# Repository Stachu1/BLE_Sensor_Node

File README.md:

# BLE Sensor Node

**BEng in Electronics Engineering thesis project, focused on low-power design and RF performance.**

A compact, coin-cell-powered Bluetooth Low Energy sensor node that measures temperature and humidity and broadcasts
the data as [BTHome](https://bthome.io/) advertisements, without needing a persistent connection.

*Rev A: `BSN-N54-A` (left), `BSN-C23-A` (middle) and the back of `BSN-C23-A` with the coin-cell holder.*

## Goal

Keep the average current low enough for multi-year operation on a single CR2032 cell, in a compact size. Main areas
of work: low-power firmware and advertising strategy, antenna/RF performance (chip vs. trace antenna), and power
budgeting around the coin cell's current limits.

## Highlights

- **Two MCUs designed, built and measured side by side** on rev A: Nordic nRF54L05 (`BSN-N54`) and TI CC2340R5
  (`BSN-C23`), with the same sensors, antenna and board outline. The CC2340R5 was chosen for rev B, mainly on sleep
  current and with RF performance as a second factor ([`MCU_DECISION.md`](hardware/MCU_DECISION.md)).
- **0.37 µA sleep floor** on BSN-C23-A, below the CC2340R5's own datasheet typical. Every event (advert, sensor
  reading, cold boot) was measured as a charge, which gives a current model for any setting: about 3.3 µA at a
  5 s advertising interval, or roughly 7 years on a 225 mAh CR2032 before derating
  ([power measurements](hardware/C23/testing/rev_A/Power/POWER_MEASUREMENTS.md)).
- **Rev A chip antenna matched on the VNA**, step by step from the unmatched antenna, with the board lifted off the
  bench (the wooden table under it had detuned the antenna) ([antenna matching](hardware/C23/testing/rev_A/RF/ANTENNA_MATCHING.md)).
- **Conducted harmonics measured on a spectrum analyser** against the FCC restricted-band limit. With no filter on
  either board, both fail on H3, the C23 by 0.6 dB and the N54 by 17 dB. With the simple pi network from TI's
  reference design the C23 passes with 9.5 dB margin. The N54's PA network, adapted from Nordic's reference design
  with 0402 parts, cost about 10 dB of output power, so it was bypassed for the measurements
  ([C23](hardware/C23/testing/rev_A/RF/RF_CARRIER.md), [N54](hardware/N54/testing/RF/RF_CARRIER.md)).
- **Rev B trace antenna designed in openEMS on the real board.** A scripted pipeline exports the KiCad board
  (all four copper layers, vias, stack-up, the CR2032) to the FDTD solver on a compute server. The chosen
  inverted-F antenna simulates at −14.9 dB S11 or better across the BLE band with two matching parts, and 85 to 89 %
  total efficiency. Simulated only, the rev B boards have not been measured yet
  ([antenna write-up](hardware/C23/testing/RF/antenna_C23-B/README.md), [simulation pipeline](hardware/C23/testing/RF/sim/README.md)).
- **Firmware for both MCUs** written to the same structure (bring-up self-test, BLE sensor, CW RF test, one power
  state per build) so the two can be measured the same way.

## Design

| `BSN-C23-B` (TI CC2340R5) | `BSN-N54-A` (Nordic nRF54L05) |
|---|---|
|  |  |
| [Schematic](hardware/C23/schematic.pdf) · [PCB](hardware/C23/PCB.pdf) · [README](hardware/C23/README.md) | [Schematic](hardware/N54/schematic.pdf) · [PCB](hardware/N54/PCB.pdf) · [README](hardware/N54/README.md) |

4-layer, 34 × 34 mm board with an HDC2010 temperature/humidity sensor, the CR2032 holder on the back and test
points for SWD, UART, I2C and the sensor interrupt.

- **Rev A (both variants):** 15.5 mm corner radii (close to round), chip antenna with a pi matching network, an
  optional U.FL connector for conducted RF tests and an SHTC3 footprint as an alternative sensor.
- **Rev B (C23 only):** 10 mm corner radii, an inverted-F antenna printed on the top layer, an MM8130 switch
  connector for VNA measurements of the antenna match, a Tag-Connect footprint for SWD, UART TX and a BOOT pin for
  the ROM bootloader, and a 0 Ω link in the supply for the ammeter. The pi network is unchanged from rev A.

## Status

Rev A of both variants was compared (thesis test T0). **Rev B uses the TI CC2340R5 (`BSN-C23-B`)** with a PCB trace
antenna, and the N54 variant stops at rev A. Rev B was ordered on 2026-11-04 (tag `hw/BSN-C23-B`). A rev C will
only be made if the rev B tests show it is needed and there is time.

The main reason is the sleep current, which sets the average current at a 5 s or slower advertising interval. RF
was also taken into account. The C23 already passes the harmonics limit with the simple pi network from TI's
reference design, so rev B starts from an RF chain that works. The N54 would need a new harmonic filter and another
RF iteration.

| | `BSN-C23-A` | `BSN-N54-A` |
|---|---|---|
| Sleep floor | 0.366 µA | 4.20 µA (System OFF 2.05 µA, both about 1.4 µA above the datasheet, cause not found) |
| Charge per advert, 0 dBm | 12.6 µC | 7.6 µC |
| Charge per sensor reading, timer / DRDY wake | 9.56 / 3.72 µC | 2.01 / 1.78 µC |
| Conducted power at the 0 dBm setting | −2.1 dBm | 0.0 dBm (PA network bypassed) |
| Harmonics with no filter, 0 dBm (conducted, FCC restricted-band limit −41.2 dBm) | H3 −40.6 dBm, fails by 0.6 dB | H3 −24.3 dBm, fails by 17 dB |
| Harmonic filter | Pi network from TI's reference design. Passes at +8 dBm (2440 and 2480 MHz) with 9.5 dB margin (H5) | PA network adapted from Nordic's reference design with 0402 parts. Lost 10–11 dB of output power and was bypassed. No working filter on this layout |
| Notes | [`hardware/C23/testing`](hardware/C23/testing) | [`hardware/N54/testing`](hardware/N54/testing) |

Rev A boards:

| Board | MCU | Status |
|---|---|---|
| `BSN-N54-A` | nRF54L05 | Ordered and assembled (2 boards). Board #1 advertising BTHome. Board #2 (U.FL): HFXO trimmed to 11.75 pF, PA network bypassed (the rev A layout of it loses 10 dB), 0.0 dBm at the 0 dBm setting. Floor 4.20 µA, 7.6 µC per advert |
| `BSN-C23-A` | CC2340R5 | Ordered and assembled. Board #1 flashed and advertising BTHome, antenna matched with the board lifted off the bench (L2 4.3 nH, L3 2.1 pF). Floor 0.366 µA, 12.6 µC per advert, about 20 µC per payload reload in the TI stack. CW boards with and without the PA pi network |

Open questions:

- The N54 floor sits about 1.4 µA above the datasheet on both boards. Not needed for the MCU choice, but still being
  looked into for the thesis.

### Next

- **Rev B bring-up** (`BSN-C23-B`): VNA match of the trace antenna against the simulation, the full-firmware check
  at a 5 s interval, the CR2032 VDD dip during TX and the H5 margin with the trace antenna.
- **Rev C** (optional): only if rev B needs fixes and time allows.
- Battery tests on fresh boards with a real CR2032, line-of-sight range tests and radiated measurements.

## Repository Structure

```
hardware/
  MCU_DECISION.md   Why rev B uses the CC2340R5
  C23/              BSN-C23 - TI CC2340R5 variant: KiCad project, schematic/PCB PDFs, testing/
  N54/              BSN-N54 - Nordic nRF54L variant (concluded at rev A)
firmware/
  C23/              Firmware for BSN-C23 boards (TI SimpleLink SDK)
  N54/              Firmware for BSN-N54 boards (nRF Connect SDK)
docs/
  datasheets/       Links to the datasheets and application notes used
  images/           Photos
```

The two MCU candidates are different chips (different pinout, power tree and BOM) rather than build options of one
board, so each has its own KiCad project under `hardware/<variant>/` and its own `firmware/<variant>/`. The N54
folders stay as the record of the rev A comparison. Only the C23 variant continues.

Test results live next to the board they were measured on, in `hardware/<variant>/testing/`, with the bring-up
procedures in `firmware/<variant>/BRINGUP.md`. The C23 rev A measurements are in `hardware/C23/testing/rev_A/`, the
rev B antenna simulations in `hardware/C23/testing/RF/`. The schematic and PCB PDFs always show the latest revision of each
board. Older revisions are in the KiCad files at their `hw/BSN-<variant>-<rev>` tags.

## Naming Scheme

Each board is identified as **`BSN-<variant>-<revision>`**, e.g. `BSN-C23-A`.

```
BSN-C23-A
 │   │  └─ PCB revision  (A, B, C …)
 │   └──── MCU variant   (C23 = TI CC2340R5, N54 = Nordic nRF54L)
 └──────── Board name    (BSN = BLE Sensor Node)
```

- **Variant:** first letter of the MCU part prefix (**n**RF54 → N, **C**C2340 → C) + MCU family number. Each variant
  has its own revision counter.
- **Revision:** bare-PCB revision, bumped only when new boards are ordered. Once gerbers are sent to the fab that
  letter is frozen. The ordered commit is tagged `hw/BSN-<variant>-<rev>`.
- **Assembly option** *(optional)*, e.g. `-UFL`: a population option on the same bare PCB. Does not change the
  revision.
- **Reworked boards** are marked `A*`, with the rework noted in the variant README.
- **The ID is on the board itself:** set in the KiCad title block and printed on the silkscreen. The firmware board
  target is `BSN_C23` / `BSN_N54`.

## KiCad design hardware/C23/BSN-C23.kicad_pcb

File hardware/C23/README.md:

# BSN-C23 (TI CC2340R5 variant)

KiCad project: `BSN-C23.kicad_pro`. See the root README for the board naming scheme. The KiCad files, the
schematic and PCB PDFs and the render show rev B. Rev A is at the tag `hw/BSN-C23-A`.

## Rev B (`BSN-C23-B`)

Ordered 2026-11-04 (tag `hw/BSN-C23-B`), not yet assembled. Same 34 × 34 mm, 4-layer board as rev A, with the
changes the rev A tests asked for. Several reference designators changed from rev A, the tables below use the rev B
names.

**Changes from rev A:**

- **Printed inverted-F antenna** (AE1, footprint `IFA_2G4`) on F.Cu along the top edge instead of the chip
  antenna. Designed with openEMS on the real board, see the [antenna write-up](testing/RF/antenna_C23-B/README.md)
  and the [simulation pipeline](testing/RF/sim/README.md). The footprint is generated by
  [`library/gen_ifa_footprint.py`](library/gen_ifa_footprint.py).
- **Corner radius 10 mm** (15.5 mm on rev A). It gives the IFA a straight ground edge of about 14 mm.
- **MM8130 switch connector (J2) instead of the U.FL.** Inserting the probe disconnects the chip side, so the VNA
  sees only the antenna and its match (L2, L3), without moving parts. The 15 pF DC block (C7) stays between the
  chip and J2.
- **Pi network unchanged** (C8, L1, C9, the rev A C7, L1, C8): same parts, placement and routing, so the rev A
  harmonics results still hold.
- **0 Ω link R1 in the supply** (VBAT to VDD), with the 2-pin header J1 across it for the ammeter. J4 is a 2-pin
  VDD/GND header for an external supply.
- **Programming and UART:** Tag-Connect TC2030-NL footprint (J3) for SWD. UART TX moved to DIO6, so with RX on
  DIO20 the ROM bootloader works over a plain USB-UART adapter. BOOT pin on DIO3 with a 100 kΩ pull-up (R4) and TP1.
- **LED D1** (with R2 1 kΩ) on DIO4, DNP by default.
- **HDC2010 INT moved from DIO21 to DIO13.** DIO21 is also the ROM bootloader's default trigger pin.
- **Removed:** U2 SHTC3 footprint, X2 (32 kHz crystal) and its load caps, the external 48 MHz load caps (the
  internal HFXT cap array trims X1). The HDC2010 is now U2.

**Population:** DNP = C6 (100 µF), D1, R2, J1, J4. AE1, J3 and the test points are copper only.

**RF network as ordered** (antenna-side values from the simulation, not yet measured):

| Ref | Value | Part | Function |
|---|---|---|---|
| C8, C9 | 1.5 pF | 490-8087-1-ND | Pi network, shunt (as rev A) |
| L1 | 2.8 nH | LQW15AN2N8G80D | Pi network, series (as rev A) |
| C7 | 15 pF | 490-11191-1-ND | DC block |
| J2 | MM8130-2600RA2 | 490-4981-1-ND | Switch connector, VNA probe on the antenna side |
| L2 | 1.6 nH | LQG15WZ1N6B02D | Antenna match, series |
| L3 | 6.8 nH | LQW15AN6N8G80D | Antenna match, shunt at J2 |
| AE1 | IFA | `IFA_2G4` (printed) | Antenna |

**Pin map** (CC2340R5 VQFN-24):

| Signal | DIO | Pin | Test point | Change from rev A |
|---|---|---|---|---|
| I2C SDA | DIO12 | 5 | TP3 | |
| I2C SCL | DIO24 | 12 | TP9 | |
| HDC2010 INT | DIO13 | 6 | TP4 | was DIO21 |
| UART TX | DIO6 | 19 | TP2 | was DIO13 |
| UART RX | DIO20 | 9 | TP8 | |
| BOOT | DIO3 | 14 | TP1 | new |
| LED | DIO4 | 15 | | new |
| SWDIO / SWCLK | DIO16 / DIO17 | 7 / 8 | TP5 / TP7 | |
| nRESET | | 13 | TP6 | |

## Rev A (`BSN-C23-A`)

This project started as a copy of `BSN-N54-A` (board outline, power, sensors, antenna and
test points), with the MCU, power tree, 48 MHz crystal, RF network and SWD pins replaced for the
CC2340R5. Rev A was exported and ordered as a separate design (not panelized).

**Population:** DNP = U2 (SHTC3), X2 (32 kHz, LFOSC is used instead), C9, C14, C15, C16, C19, C20,
J1 (U.FL), L4. Everything else is fitted.

**RF network as fitted** (values from the TI reference design, not tuned for this board):

| Ref | Value | Part |
|---|---|---|
| C7, C8 | 1.5 pF | 490-8087-1-ND |
| L1 | 2.8 nH | LQW15AN2N8G80D |
| C6 | 15 pF | 490-11191-1-ND |
| L2 | 6.7 nH | LQW15AN6N7B00D |
| L3 | 7.3 nH | 490-6844-1-ND |
| AE1 | Chip antenna | AANI-CH-0138-Q-T |

**Tuned antenna match** (VNA, board lifted off the bench, see below): L2 = **4.3 nH**, **2.1 pF** on the
L3 pads instead of the 7.3 nH. Fitted on board #1 (2026-10-26).

### Bring-up status

Procedure and per-board results: [`firmware/C23/BRINGUP.md`](../../firmware/C23/BRINGUP.md).

| Board | BLE address | Status |
|---|---|---|
| #1 | FC:DE:C5:73:2F:4E | Flashes over SWD. `hwtest` 13/13 PASS. `ble_sensor` advertises BTHome and readings are received on the PC with `tools/bsn_scan.py`. A\*: antenna side matched (L2 4.3 nH, 2.1 pF on the L3 pads). **U2 (SHTC3) is fitted.** Floor 0.366 µA, 16.1 µA with 1 s advertising, see [Current measurements](#current-measurements). |
| RF test | (no MCU) | Antenna-only board used for VNA matching, see below. |
| RF CW | | MCU, X1, pi network (C7/L1/C8) and J1 only, no antenna. Used with `cwtest` for the carrier frequency and output power, see [`testing/rev_A/RF/RF_CARRIER.md`](testing/rev_A/RF/RF_CARRIER.md): HFXT trim set to 44 (+2.2 ppm), +6.7 dBm at the +8 dBm setting. |
| RF CW no-pi | | As RF CW, but with the PA-side pi network removed (see the rework log). `hwtest` PASS. For the conducted power and harmonics comparison with RF CW. |

### Current measurements

Full notes and data: [`testing/rev_A/Power/POWER_MEASUREMENTS.md`](testing/rev_A/Power/POWER_MEASUREMENTS.md).

Board #1 at 3.0 V: sleep floor **0.366 µA** (with or without the BLE stack). One advertising event at 0 dBm costs
**12.6 µC** (+34 % at 2.0 V, −8 % at −8 dBm, +116 % at +8 dBm). A sensor reading costs **9.56 µC** with timer polling
and **3.72 µC** when the HDC2010 auto mode wakes the MCU over DRDY. The full `ble_sensor` (1 s advertising, sensor
every 10 s) averages **16.1 µA**. The SHTC3, if fitted, idles at about 45 µA after power-on until the firmware puts it
to sleep. Always clear the debug state with a full power-on reset before measuring (see the notes).

### Antenna matching

Full notes and data: [`testing/rev_A/RF/ANTENNA_MATCHING.md`](testing/rev_A/RF/ANTENNA_MATCHING.md).

The TI reference values don't fit this layout. At 2.44 GHz the bare antenna is about 6.4 − j13 Ω (flat on
the table), and 6.7 nH for L2 is about three times too much. On the RF-only test board (Keysight P9370B through J1):

| Date | Configuration | L2 (series) | L3 pads (shunt) | S11 at 2.44 GHz | Worst in 2.40–2.48 GHz |
|---|---|---|---|---|---|
| — | TI reference | 6.7 nH | 7.3 nH | not measured | — |
| 2026-10-23 | Matched, flat on a wooden table | 3.3 nH | 2.0 pF | −18.8 dB | −11.0 dB |
| 2026-10-23 | Same, lifted | 3.3 nH | 2.0 pF | −3.1 dB (9.5 + j12.3 Ω) | — |
| 2026-10-26 | **Matched, lifted** | **4.3 nH** | **2.1 pF** | **−32.1 dB** | **−10.3 dB** |

The first match was tuned flat on a wooden table, which detuned the antenna. Lifted about 5 mm (by the battery
holder), the impedance was about the same as with the board hanging in the air, and the coin cell in or out made
almost no difference. **Use 4.3 nH + 2.1 pF**, and tune with the board lifted or in its final position.
Until they are fitted on a working board, RSSI and range numbers from board #1 (reference values) are
only a pre-tuning baseline.

### Rework log

Hand-modified boards are marked `A*` (see the root README).

| Board | Date | Change | Reason |
|---|---|---|---|
| RF test | 2026-10-23 | No MCU, C8 or L1. J1 (U.FL) fitted, one 15 pF series bridged, L2 = 3.3 nH, 2.0 pF on the L3 pads | Antenna matching with a VNA |
| RF test | 2026-10-26 | Battery holder fitted, L2 = 4.3 nH, 2.1 pF on the L3 pads | Re-match with the board lifted off the table |
| #1 | 2026-10-26 | L2 = 4.3 nH, 2.1 pF on the L3 pads (antenna side). PA-side pi network unchanged (TI reference) | Fit the tuned match |
| RF CW no-pi | 2026-10-27 | MCU, X1 and J1 only. C7 and C8 not fitted, L1 shorted with solder, 15 pF series cap to J1 kept as the DC block | Check whether the pi network is needed for harmonics, and its effect on output power |

Known issues to fix in rev B are listed at the end of [`BRINGUP.md`](../../firmware/C23/BRINGUP.md#notes-for-rev-b).

## CC2340R5 design resources

There is no CC2340 part in the official KiCad library and no TI equivalent of Nordic's
KiCad design blocks, so the design blocks table is empty for now.

| Resource | Format | Link |
|---|---|---|
| CC2340R5 symbol + footprint + STEP (RGE VQFN-24 4x4) | KiCad v6+ export via Ultra Librarian (free login) | https://vendor.ultralibrarian.com/TI/embedded/?gpn=CC2340R5&package=RGE&pin=24 |
| LP-EM-CC2340R53 LaunchPad design files (uses the 40-pin RKP package, but the RF, crystal and DC/DC circuits carry over) | Allegro/OrCAD + schematic/layout PDF, BOM, Gerbers, ODB++ | https://www.ti.com/lit/zip/SWRC397 |
| LP-EM-CC2340R53 user guide | PDF | https://www.ti.com/lit/pdf/SWRU637 |
| CC234x/CC27xx hardware configuration & PCB design (SWRA834) | PDF | https://www.ti.com/lit/pdf/SWRA834 |
| Product page (packages, docs) | Web | https://www.ti.com/product/CC2340R5 |

### CC2340R5 part in the `BSN-C23` library

| Part | Symbol | Footprint | 3D model |
|---|---|---|---|
| CC2340R52E0RGER (VQFN-24 4x4) | `CC2340R52E0RGER` | `Texas_RGE0024B_VQFN-24-1EP_4x4mm_P0.5mm_EP2.45x2.45mm_ThermalVias` | `Texas_RGE0024H_VQFN-24-1EP_4x4mm_P0.5mm_EP2.7x2.7mm.step` |

These were made here from the datasheet and KiCad's stock library rather than downloaded:

- **Symbol:** drawn from the datasheet (SWRS272F), Figure 6-2 and Tables 6-1 to 6-13. The exposed pad is pin 25 (GND).
- **Footprint:** KiCad's stock `VQFN-24-1EP_4x4mm_P0.5mm_EP2.45x2.45mm_ThermalVias`, renamed. It matches TI's RGE0024B land pattern (2.45 mm pad, 9 vias on a 0.975 mm grid). The signal pads are 0.775 mm long versus 0.6 mm in TI's example.
- **3D model:** KiCad has no STEP file for the 2.45 mm pad version. This one is the TI RGE0024H body, which is identical apart from a 2.7 mm exposed pad hidden under the package.

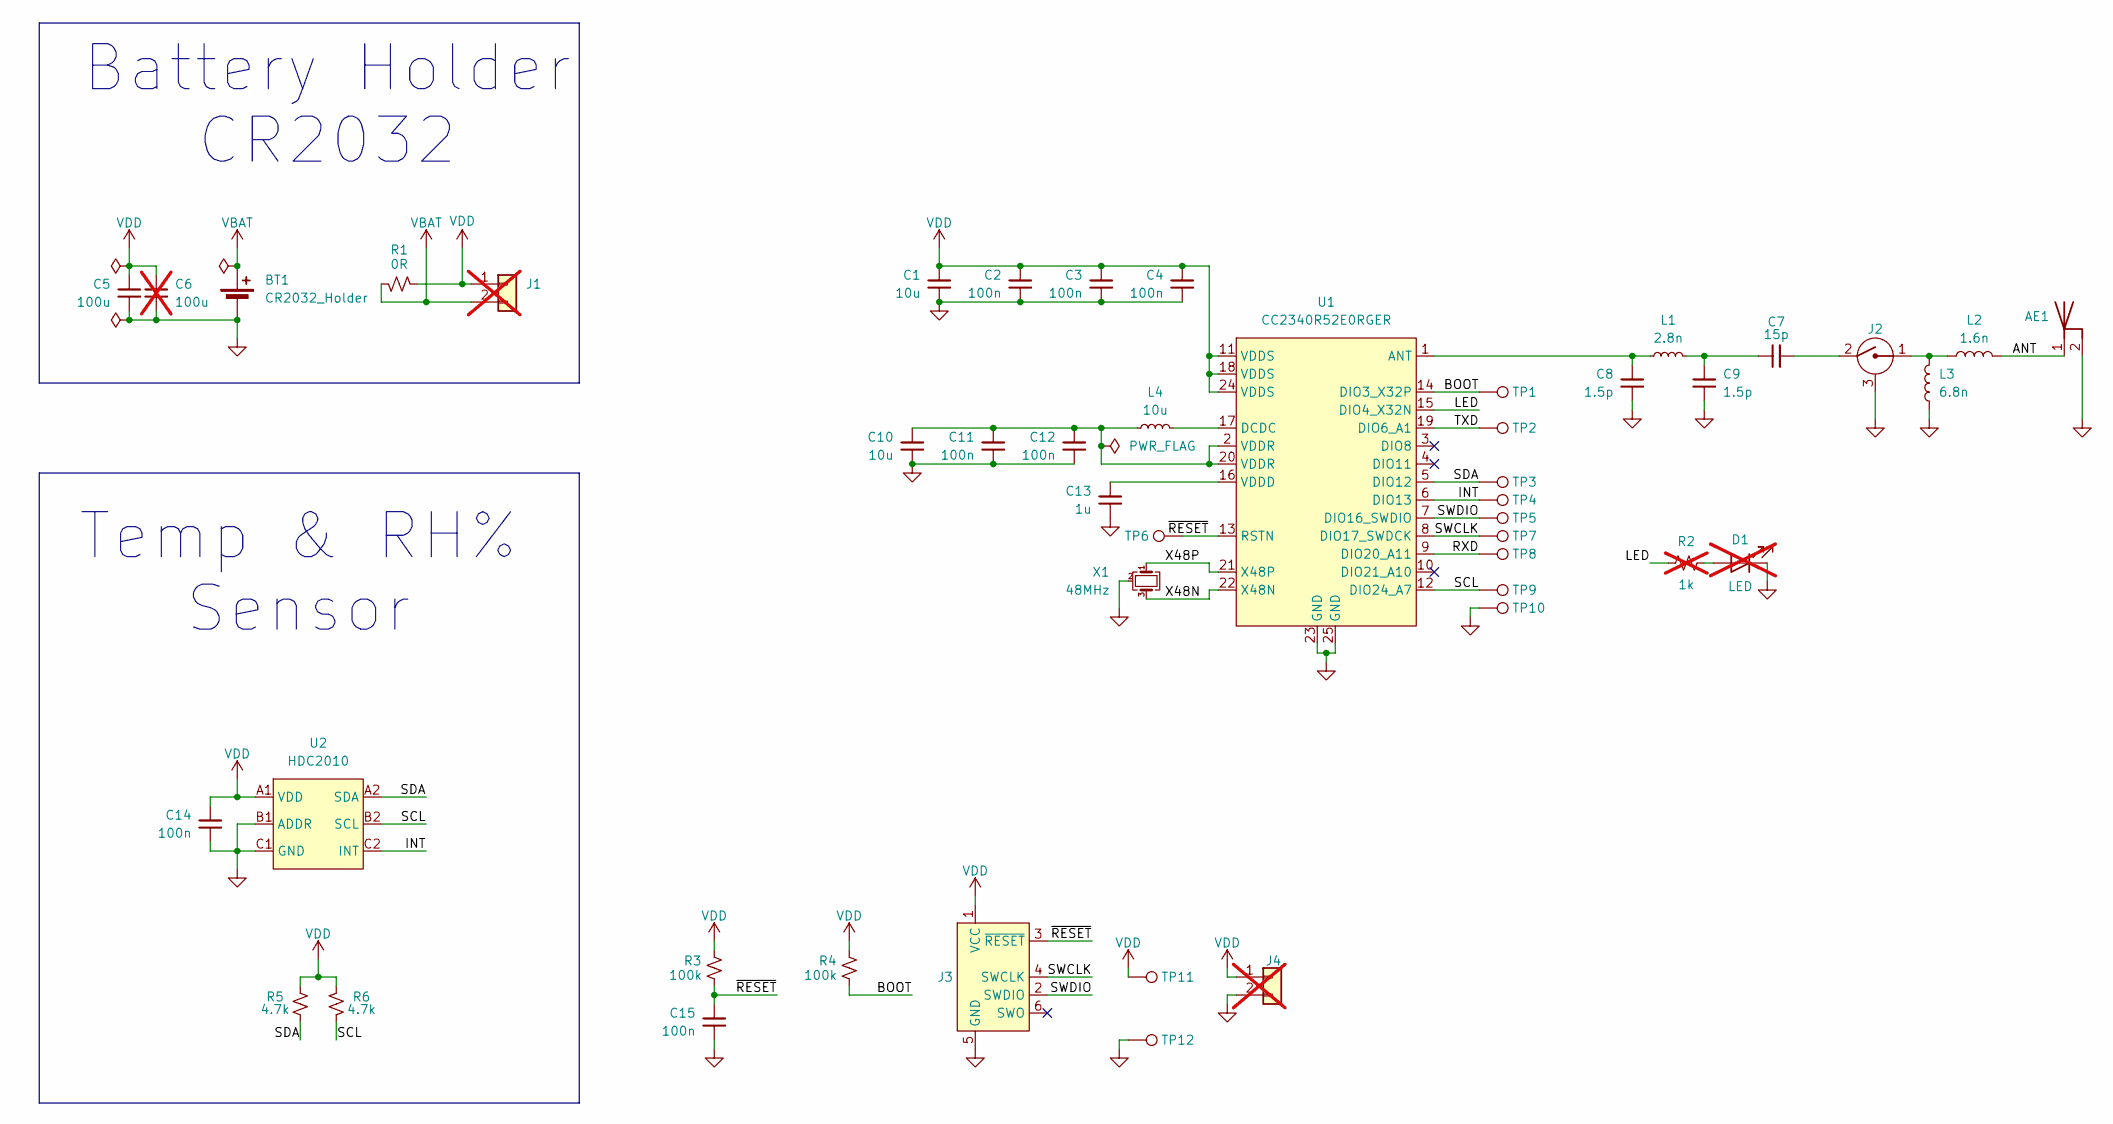
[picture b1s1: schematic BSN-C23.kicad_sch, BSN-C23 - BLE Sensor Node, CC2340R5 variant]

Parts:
AE1: IFA_2G4
BT1: CR2032_Holder; BatteryHolder_Renata_SMTU2032-LF_1x2032; DigiKey 123-A-BAT-CH-C8-EA-ZSR3CT-ND
C1, C10: 10u; C_0603_1608Metric
C2, C3, C4, C11, C12, C14, C15: 100n; C_0402_1005Metric
C5: 100u; C_0805_2012Metric; DigiKey 490-GRM21BR60J107ME15KCT-ND
C6: 100u; C_0805_2012Metric; DigiKey 490-GRM21BR60J107ME15KCT-ND; not fitted
C7: 15p; C_0402_1005Metric; DigiKey 490-11191-1-ND
C8, C9: 1.5p; C_0402_1005Metric; DigiKey 490-8087-1-ND
C13: 1u; C_0402_1005Metric
D1: LED; LED_0603_1608Metric; DigiKey 475-LOQ976.01-P2R2-25-1-20-R18CT-ND; not fitted
J1, J4: Conn_01x02; PinHeader_1x02_P2.00mm_Vertical; DigiKey 952-2273-ND; not fitted
J2: MM8130-2600RA2; Murata_MM8130-2600; DigiKey 490-4981-1-ND
J3: Conn_ARM_SWD_TagConnect_TC2030-NL; Tag-Connect_TC2030-IDC-NL_2x03_P1.27mm_Vertical
L1: 2.8n; L_0402_1005Metric; DigiKey 490-LQW15AN2N8G80DCT-ND
L2: 1.6n; L_0402_1005Metric; DigiKey 490-LQG15WZ1N6B02DCT-ND
L3: 6.8n; L_0402_1005Metric; DigiKey 490-14714-1-ND
L4: 10u; L_0603_1608Metric
R1: 0R; R_0402_1005Metric; DigiKey P0.0JCT-ND
R2: 1k; R_0402_1005Metric; not fitted
R3, R4: 100k; R_0402_1005Metric
R5, R6: 4.7k; R_0402_1005Metric
TP1, TP2, TP3, TP4, TP5, TP6, TP7, TP8, TP9, TP10, TP11, TP12: TestPoint; TestPoint_Pad_D1.0mm
U1: CC2340R52E0RGER; Texas_RGE0024B_VQFN-24-1EP_4x4mm_P0.5mm_EP2.45x2.45mm_Therm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; DigiKey 296-CC2340R52E0RGERCT-ND
U2: HDC2010; DigiKey 296-47774-1-ND
X1: 48MHz; Crystal_SMD_3225-4Pin_3.2x2.5mm; DigiKey 50-ECS-480-8-33B-CWN-TR3CT-ND

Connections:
/ANT: AE1.1 (Feed), L2.2
/BOOT: R4.1, TP1.1 (1_1), U1.14 (DIO3_X32P)
/INT: TP4.1 (1_1), U1.6 (DIO13), U2.C2 (INT)
/LED: R2.1, U1.15 (DIO4_X32N)
/RXD: TP8.1 (1_1), U1.9 (DIO20_A11)
/SCL: R6.1, TP9.1 (1_1), U1.12 (DIO24_A7), U2.B2 (SCL)
/SDA: R5.1, TP3.1 (1_1), U1.5 (DIO12), U2.A2 (SDA)
/SWCLK: J3.4 (SWCLK), TP7.1 (1_1), U1.8 (DIO17_SWDCK)
/SWDIO: J3.2 (SWDIO), TP5.1 (1_1), U1.7 (DIO16_SWDIO)
/TXD: TP2.1 (1_1), U1.19 (DIO6_A1)
/X48N: U1.22 (X48N), X1.3
/X48P: U1.21 (X48P), X1.1
/~RESET: C15.1, J3.3 (~RESET), R3.1, TP6.1 (1_1), U1.13 (RSTN)
GND: AE1.2 (GND), BT1.2 (-), C1.2, C2.2, C3.2, C4.2, C5.2, C6.2, C8.2, C9.2, C10.2, C11.2, C12.2, C13.2, C14.2, C15.2, D1.1 (K), J2.3, J3.5 (GND), J4.2, L3.1, TP10.1 (1_1), TP12.1 (1_1), U1.23 (GND), U1.25 (GND), U2.B1 (ADDR), U2.C1 (GND), X1.2 (G), X1.4 (G)
unnamed: C7.1, J2.2
unnamed: C7.2, C9.1, L1.2
unnamed: C10.1, C11.1, C12.1, L4.1, U1.2 (VDDR), U1.20 (VDDR)
unnamed: D1.2 (A), R2.2
unnamed: J2.1, L2.1, L3.2
unnamed: C8.1, L1.1, U1.1 (ANT)
unnamed: L4.2, U1.17 (DCDC)
unnamed: C13.1, U1.16 (VDDD)
VBAT: BT1.1 (+), J1.2, R1.1
VDD: C1.1, C2.1, C3.1, C4.1, C5.1, C6.1, C14.1, J1.1, J3.1 (VCC), J4.1, R1.2, R3.2, R4.2, R5.2, R6.2, TP11.1 (1_1), U1.11 (VDDS), U1.18 (VDDS), U1.24 (VDDS), U2.A1 (VDD)

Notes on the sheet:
Battery Holder CR2032
Temp & RH% Sensor

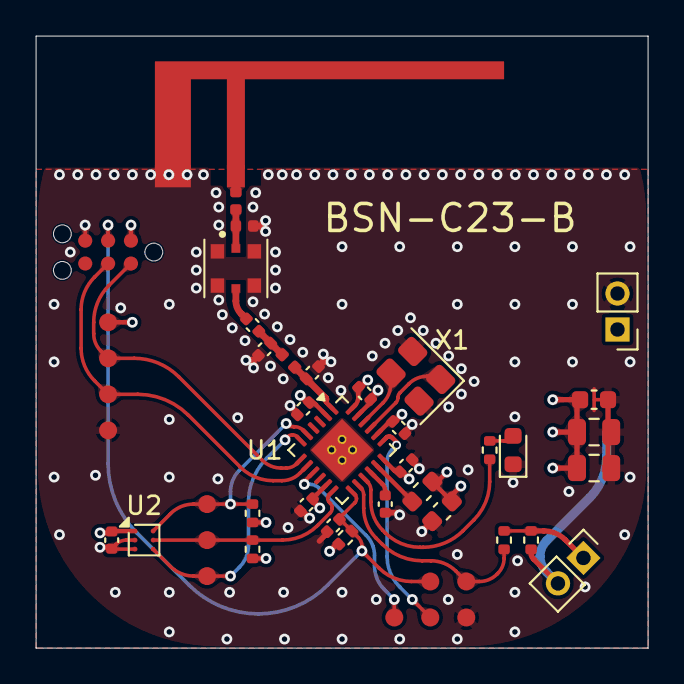
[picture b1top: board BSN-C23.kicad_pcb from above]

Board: 4 copper layers, 34.0 x 34.0 mm, 47 parts (1 on the bottom side), 24 nets.

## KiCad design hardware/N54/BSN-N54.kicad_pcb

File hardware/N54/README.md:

# BSN-N54 (Nordic nRF54L variant)

> **Concluded at rev A.** The N54 was compared with the C23 on rev A, and rev B uses the CC2340R5. See
> [`MCU_DECISION.md`](../MCU_DECISION.md). This folder is kept as the record of that comparison.

KiCad project: `BSN-N54.kicad_pro`. See the root README for the board naming scheme.

## Rev A (`BSN-N54-A`)

Ordered as a separate design from BSN-C23-A (not panelized). Firmware, bring-up procedure and per-board
results: [`firmware/N54`](../../firmware/N54) and [`firmware/N54/BRINGUP.md`](../../firmware/N54/BRINGUP.md).

### Bring-up status

| Board | BLE address | Status |
|---|---|---|
| #1 | EC:A6:80:CE:7A:1A | Full build except U2 (SHTC3) and X2 (32 kHz). `hwtest` 13/13 PASS. `ble_sensor` advertises BTHome and is decoded with `tools/bsn_scan.py`. Antenna side fitted with the C23 values (L6 4.3 nH, 2.1 pF shunt), **not verified on this layout** (see below). PA network as designed, which loses about 10 dB (see board #2). |
| #2 | FA:28:B5:E0:85:F5 | MCU + U.FL, no antenna, no U2/X2. `hwtest` 13/13 PASS. A\*: PA network bypassed. Used for the crystal trim, conducted power and the current measurements. |

### Test results

- **RF:** [`testing/RF/RF_CARRIER.md`](testing/RF/RF_CARRIER.md). HFXO trim 11.75 pF (+127 ppm at the datasheet
  7 pF). The reference PA network as laid out costs 10–11 dB. Bypassed, the PA gives 0.0 dBm at the 0 dBm
  setting and +7.5 dBm at +8 dBm.
- **Current:** [`testing/Power/POWER_MEASUREMENTS.md`](testing/Power/POWER_MEASUREMENTS.md). Floor 4.20 µA
  (System OFF 2.05 µA, both about 1.4 µA above the datasheet on both boards, cause not found), 7.6 µC per advert
  at 0 dBm, 2.01 / 1.78 µC per sensor reading with timer / DRDY wake (C23: 0.366 µA, 12.6 µC, 9.56 / 3.72 µC).

### Rework log

Hand-modified boards are marked `A*` (see the root README).

| Board | Date | Change | Reason |
|---|---|---|---|
| #1 | 2026-10-27 | Antenna side: 4.3 nH series and 2.1 pF shunt (the C23 match) | Same antenna as C23. Not re-matched: AE1 is fed from the other end than on C23 (rotated 180°, feed pad at x = 146.75 instead of 153.25) through a longer trace, so the match is only a starting point |
| #2 | 2026-10-27 | X1 reflowed | Checking the +127 ppm offset (no change) |
| #2 | 2026-10-27 | PA network bypassed: 15 pF in series at L2 (DC block), L3 and L4 bridged, C14, C15, C16 removed. R4 0 Ω and J1 kept | The network cost 10–11 dB. Bypassed, the output matches the datasheet |
| #2 | 2026-10-27 | Cleaned with IPA | Checking whether flux explains the high floor current (no change) |

## ANT-pin matching network

The antenna matching network on the nRF54L05 ANT pin (U1 pin 31) is the Nordic reference PA network (nRF54L
datasheet, circuit configuration 1 for QFN48: L2, C14, L3, C15, L4, C16), followed by the antenna match (L5, L6, L7)
and the U.FL test point (R4, J1).

```
U1.ANT(31) ─ L2 ─┬─ L3 ─┬─ L4 ─┬──────────── L6 ─┬─ AE1
               C14    C15    C16   L5      │     L7
                │      │      │    │      R4     │
              VSS_PA  GND    GND  GND      │    GND
             (pin 32)                     J1
```

| Ref | Value | Role |
|---|---|---|
| L2, C14, L3, C15, L4, C16 | 2.7 nH, 1.5 pF, 3.5 nH, 2.0 pF, 3.5 nH, 0.3 pF | Nordic reference PA network (0201 in the reference, 0402 here) |
| L5 | 7.3 nH | Shunt to GND on the J1 node (antenna side) |
| L6 | 6.7 nH | Series to the antenna |
| L7 | | Shunt at the antenna feed |
| R4, J1 | 0 Ω, U.FL | Test point, not fitted in normal use |

C14 grounds only to pin 32 (VSS_PA), which only joins the centre pad, and C15 grounds straight to the bottom plane
with no inner-layer fill, as Nordic's notes require.

**Measured on rev A:** this network, as laid out with 0402 parts, cost 10–11 dB into 50 Ω (see
[`testing/RF/RF_CARRIER.md`](testing/RF/RF_CARRIER.md)). A rev B N54 should copy Nordic's 0201 layout exactly and
verify the PA network into 50 Ω on its own before the antenna is matched.

### Original Smith chart estimate (superseded)

Before the boards existed, the MCU source impedance and the antenna impedance were estimated from the nRF54L and
antenna datasheets and stepped through all 8 elements on a Smith chart. This treated L5 as a series part, which it
isn't on the board, and the estimated antenna impedance was later measured on C23 to be quite different
(about 6.4 − j13 Ω, see `hardware/C23/testing/rev_A/RF/ANTENNA_MATCHING.md`). Kept for reference:

https://onlinesmithchart.com/?circuit=blackBox_34.1_-40.9_0__seriesInd_2.7_nH_0_0__shortedCap_1.5_pF_0_0_0__seriesInd_3.5_nH_0_0__shortedCap_2_pF_0_0_0__seriesInd_3.5_nH_0_0__shortedCap_0.3_pF_0_0_0__shortedInd_7.3_nH_0_0__seriesInd_6.7_nH_0_0&fSpan=0

A simplified 3-element equivalent from the same estimate:

https://onlinesmithchart.com/?circuit=blackBox_34.1_-40.9_0__seriesInd_4.2_nH_0_0__shortedCap_0.3_pF_0_0_0__seriesInd_6.7_nH_0_0&fSpan=0

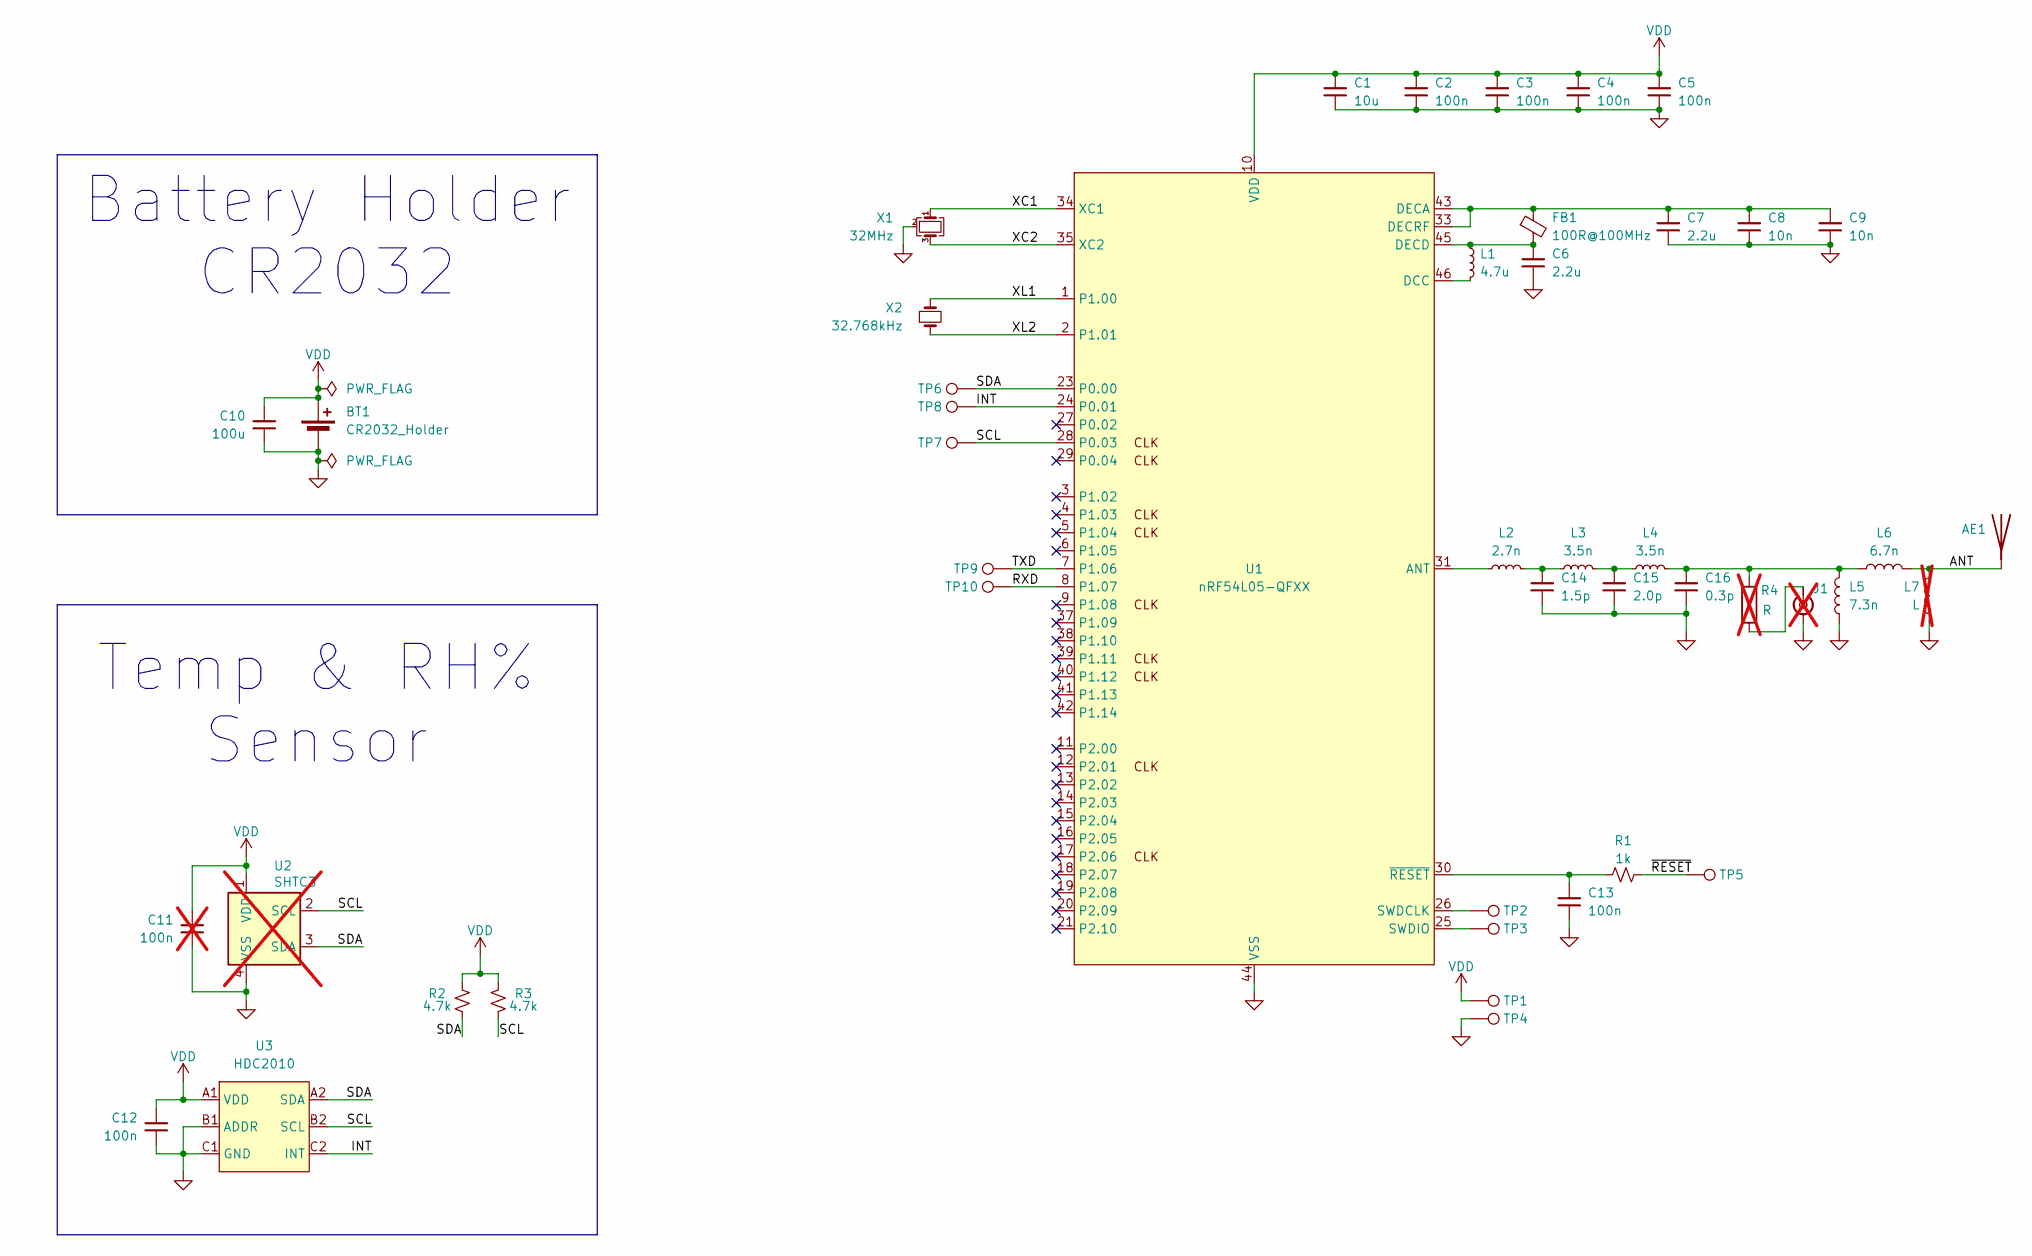
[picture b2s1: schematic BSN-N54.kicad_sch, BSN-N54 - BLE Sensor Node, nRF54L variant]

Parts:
AE1: AANI-CH-0138-Q-T; DigiKey 535-AANI-CH-0138-Q-TCT-ND
BT1: CR2032_Holder; BatteryHolder_Renata_SMTU2032-LF_1x2032; DigiKey 123-A-BAT-CH-C8-EA-ZSR3CT-ND
C1: 10u; C_0603_1608Metric
C2, C3, C4, C5, C12, C13: 100n; C_0402_1005Metric
C6, C7: 2.2u; C_0402_1005Metric; DigiKey 445-9028-1-ND
C8, C9: 10n; C_0402_1005Metric; DigiKey 490-4516-1-ND
C10: 100u; C_0805_2012Metric; DigiKey 490-GRM21BR60J107ME15KCT-ND
C11: 100n; C_0402_1005Metric; not fitted
C14: 1.5p; C_0402_1005Metric; DigiKey 490-8087-1-ND
C15: 2.0p; C_0402_1005Metric; DigiKey 490-11205-1-ND
C16: 0.3p; C_0402_1005Metric; DigiKey 490-11248-1-ND
FB1: 100R@100MHz; L_0603_1608Metric
J1: Conn_Coaxial_Small; U.FL_Hirose_U.FL-R-SMT-1_Vertical; DigiKey H11891CT-ND; not fitted
L1: 4.7u; L_0603_1608Metric; DigiKey 490-12065-1-ND
L2: 2.7n; L_0402_1005Metric; DigiKey 490-15398-1-ND
L3, L4: 3.5n; L_0402_1005Metric; DigiKey 490-15430-1-ND
L5: 7.3n; L_0402_1005Metric; DigiKey 490-6844-1-ND
L6: 6.7n; L_0402_1005Metric; DigiKey 490-LQW15AN6N7B00DCT-ND
L7: L; L_0402_1005Metric; not fitted
R1: 1k; R_0402_1005Metric
R2, R3: 4.7k; R_0402_1005Metric
R4: R; R_0201_0603Metric; not fitted
TP1, TP2, TP3, TP4: TestPoint; TestPoint_Pad_D1.5mm
TP5, TP6, TP7, TP8, TP9, TP10: TestPoint; TestPoint_Pad_D1.0mm
U1: nRF54L05-QFXX; VQFN-48-1EP_6x6mm_P0.4mm_EP4.1x4.1mm_ThermalVias; DigiKey 4823-NRF54L05-QFAA-RCT-ND
U2: SHTC3; Sensirion_DFN-4-1EP_2x2mm_P1mm_EP0.7x1.6mm; DigiKey 1649-SHTC3-TR-2.5KSCT-ND; not fitted
U3: HDC2010; DigiKey 296-47774-1-ND
X1: 32MHz; Crystal_SMD_3225-4Pin_3.2x2.5mm; DigiKey 478-CX3225FB32000C0FZZH1CT-ND
X2: 32.768kHz; Crystal_SMD_3215-2Pin_3.2x1.5mm; DigiKey 728-1074-1-ND

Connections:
/ANT: AE1.1 (Feed_1), L6.2, L7.1
/INT: TP8.1 (1_1), U1.24 (P0.01), U3.C2 (INT)
/RXD: TP10.1 (1_1), U1.8 (P1.07)
/SCL: R3.1, TP7.1 (1_1), U1.28 (P0.03), U2.2 (SCL), U3.B2 (SCL)
/SDA: R2.1, TP6.1 (1_1), U1.23 (P0.00), U2.3 (SDA), U3.A2 (SDA)
/TXD: TP9.1 (1_1), U1.7 (P1.06)
/XC1: U1.34 (XC1), X1.1
/XC2: U1.35 (XC2), X1.3
/XL1: U1.1 (P1.00), X2.2
/XL2: U1.2 (P1.01), X2.1
/~RESET: R1.2, TP5.1 (1_1)
GND: BT1.2 (-), C1.2, C2.2, C3.2, C4.2, C5.2, C6.2, C7.2, C8.2, C9.2, C10.2, C11.2, C12.2, C13.2, C14.2, C15.2, C16.2, J1.2 (Ext), L5.1, L7.2, TP4.1 (1_1), U1.32 (VSS_PA), U1.44 (VSS), U1.49 (VSS), U2.4 (VSS), U3.B1 (ADDR), U3.C1 (GND), X1.2 (G), X1.4 (G)
unnamed: C14.1, L2.2, L3.1
unnamed: C15.1, L3.2, L4.1
unnamed: C16.1, L4.2, L5.2, L6.1, R4.1
unnamed: J1.1 (In), R4.2
unnamed: L2.1, U1.31 (ANT)
unnamed: L1.2, U1.46 (DCC)
unnamed: C7.1, C8.1, C9.1, FB1.1, U1.33 (DECRF), U1.43 (DECA)
unnamed: C6.1, FB1.2, L1.1, U1.45 (DECD)
unnamed: TP2.1 (1_1), U1.26 (SWDCLK)
unnamed: TP3.1 (1_1), U1.25 (SWDIO)
unnamed: C13.1, R1.1, U1.30 (~RESET)
VDD: BT1.1 (+), C1.1, C2.1, C3.1, C4.1, C5.1, C10.1, C11.1, C12.1, R2.2, R3.2, TP1.1 (1_1), U1.10 (VDD), U1.22 (VDD), U1.36 (VDD), U1.47 (VDD), U1.48 (VDD), U2.1 (VDD), U3.A1 (VDD)

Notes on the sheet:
Battery Holder CR2032
Temp & RH% Sensor

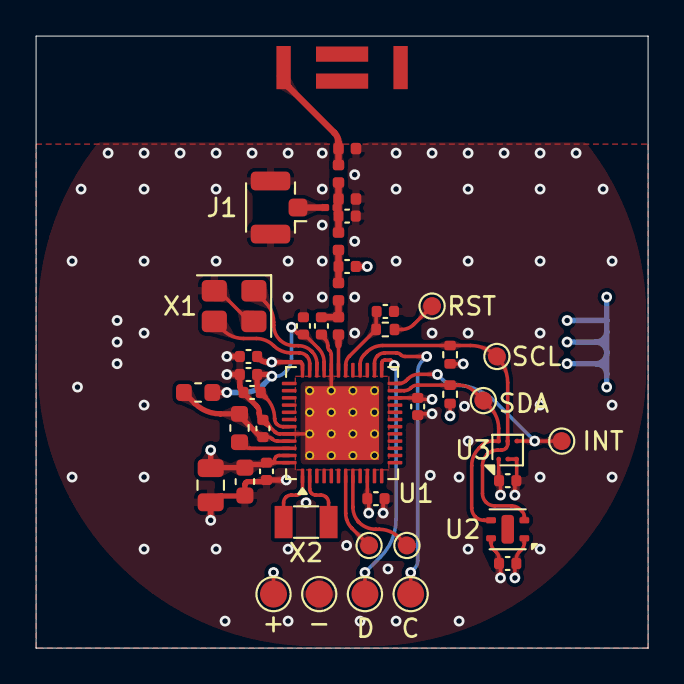
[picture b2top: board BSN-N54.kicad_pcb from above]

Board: 4 copper layers, 34.0 x 34.0 mm, 46 parts (1 on the bottom side), 24 nets.

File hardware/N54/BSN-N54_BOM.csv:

"Reference","Qty","Value","DigiKey","AX"
"AE1","1","AANI-CH-0138-Q-T","535-AANI-CH-0138-Q-TCT-ND",""
"BT1","1","CR2032_Holder","123-A-BAT-CH-C8-EA-ZSR3CT-ND",""
"C1","1","10u","","27204"
"C2,C3,C4,C5,C12,C13","6","100n","","27726"
"C6,C7","2","2.2u","490-12731-1-ND",""
"C8,C9","2","10n","490-3194-1-ND",""
"C10","1","100u","490-9969-1-ND",""
"C14","1","1.5p","490-8087-1-ND",""
"C15","1","2.0p","490-11205-1-ND",""
"C16","1","0.3p","490-17132-1-ND",""
"FB1","1","100R@100MHz","","73236"
"J1","1","Conn_Coaxial_Small","H11891CT-ND",""
"L1","1","4.7u","490-12065-1-ND",""
"L2","1","2.7n","490-15398-1-ND",""
"L3,L4","2","3.5n","490-15430-1-ND",""
"L5","1","7.3n","490-6844-1-ND",""
"L6","1","6.7n","490-LQW15AN6N7B00DCT-ND",""
"R1","1","1k","","201001"
"R2,R3","2","4.7k","","204701"
"U1","1","nRF54L05-QFXX","4823-NRF54L05-QFAA-RCT-ND",""
"U2","1","SHTC3","1649-SHTC3-TR-2.5KSCT-ND",""
"U3","1","HDC2010","296-47774-1-ND",""
"X1","1","32MHz","478-CX3225FB32000C0FZZH1CT-ND",""
"X2","1","32.768kHz","728-1074-1-ND",""
